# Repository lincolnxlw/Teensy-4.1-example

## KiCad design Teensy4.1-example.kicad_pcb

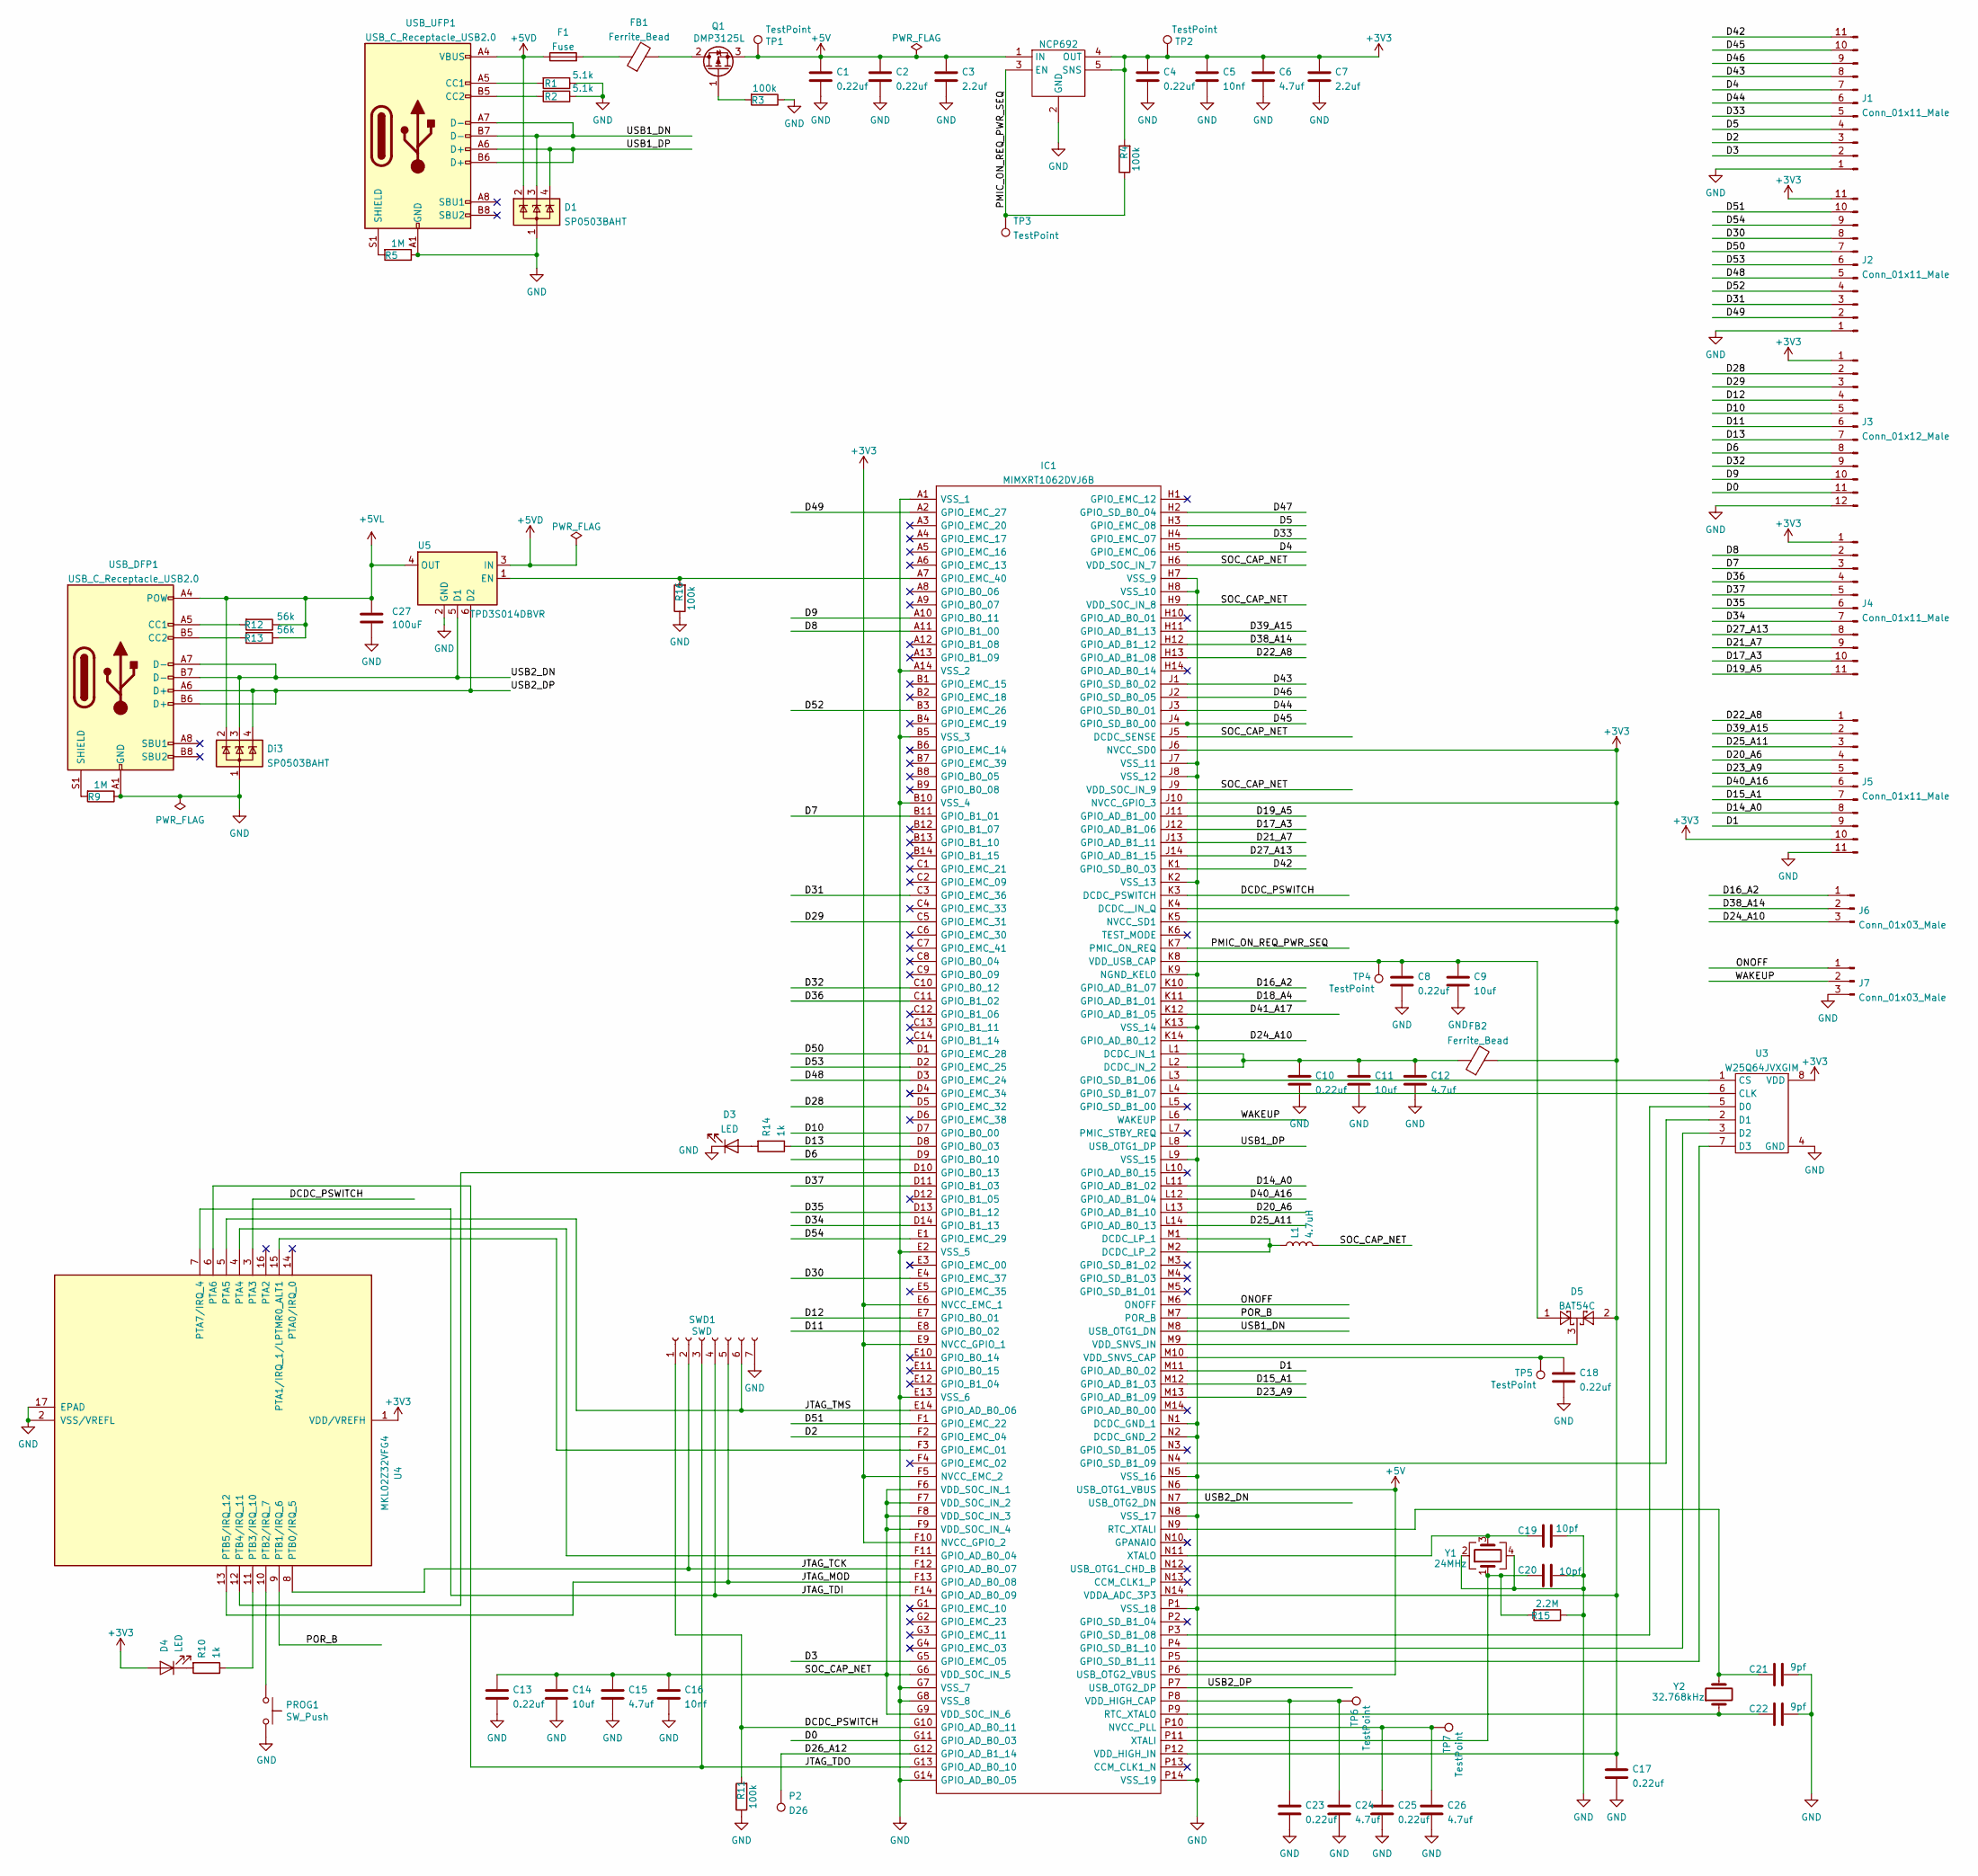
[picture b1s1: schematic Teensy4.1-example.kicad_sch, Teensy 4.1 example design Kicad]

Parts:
C1, C2, C4, C8, C10, C13, C17, C18, C23, C25: 0.22uf; C_0603_1608Metric; MPN CC0603KRX7R6BB224; LCSC C106216
C3, C7: 2.2uf; C_0603_1608Metric; MPN CL10B225KP8NNNC; LCSC C100082
C5, C16: 10nf; C_0603_1608Metric; MPN 0603B103K160CT; LCSC C163173
C6, C12, C15, C24, C26: 4.7uf; C_0603_1608Metric; MPN CL10B475KQ8NQNC; LCSC C107368
C9, C11, C14: 10uf; C_0805_2012Metric; MPN GRM21BR71A106KA73K; LCSC C2167686
C19, C20: 10pf; C_0603_1608Metric; MPN CC0603KRX7R6BB224; LCSC C1634
C21, C22: 9pf; C_0603_1608Metric; MPN GRM1885C1H9R0DA01D; LCSC C430713
C27: 100uF; C_1206_3216Metric; LCSC C883598
D1: SP0503BAHT; SOT-143; LCSC C3040626
D3, D4: LED; LED_0402_1005Metric; LCSC C264407
D5: BAT54C; SOT-23; LCSC C266596
Di3: SP0503BAHT; SOT-143; LCSC C3040626
F1: Fuse; R_0805_2012Metric; MPN 0ZCK0050FF2E; LCSC C5220829
FB1, FB2: Ferrite_Bead; R_0805_2012Metric; MPN FBMH2012HM121-T‎; LCSC C454098
IC1: MIMXRT1062DVJ6B; BGA196C80P14X14_1200X1200X152; Mouser Part Number 771-MIMXRT1062DVJ6B
J1, J2, J4, J5: Conn_01x11_Male; PinHeader_1x11_P2.54mm_Vertical
J3: Conn_01x12_Male; PinHeader_1x12_P2.54mm_Vertical
J6, J7: Conn_01x03_Male; PinHeader_1x03_P2.54mm_Vertical
L1: 4.7uH; C_0805_2012Metric; MPN LQM21PN4R7MGRD; LCSC C86090
NCP692: OnSemi NCP692, fixed version; DFN-6-1EP_3x3mm_P0.95mm_EP1.7x2.6mm; MPN NCP692MN33T2G; LCSC C145519
P2: D26; PinHeader_1x01_P1.00mm_Vertical
PROG1: SW_Push; KMR241GLFS; MPN KMR241GLFS; LCSC C221682
Q1: DMP3125L; SOT-23; LCSC C459542
R1, R2: 5.1k; R_0603_1608Metric; MPN RC0603FR-075K1L; LCSC C105580
R3, R4, R11, R16: 100k; R_0603_1608Metric; LCSC C15458
R5, R9: 1M; R_0603_1608Metric; LCSC C22935
R10, R14: 1k; R_0402_1005Metric; LCSC C11702
R12, R13: 56k; R_0603_1608Metric; MPN RMCF0603FT56K0; LCSC C23206
R15: 2.2M; R_0603_1608Metric; LCSC C18679
SWD1: SWD; PinHeader_1x07_P1.27mm_Vertical
TP1, TP2, TP3, TP4, TP5, TP6, TP7: TestPoint; TestPoint_Pad_D1.0mm
U3: W25Q64JVXGIM; XSON8_4x4mm; LCSC C5440778
U4: MKL02Z32VFG4; QFN-16-1EP_3x3mm_P0.5mm_EP1.8x1.8mm; MPN Custom firmware part
U5: TPD3S014DBVR; SOT-23-6; LCSC C87384
USB_DFP1: USB_C_Receptacle_USB2.0; TYPE-C-31-M-14; LCSC C223907
USB_UFP1: USB_C_Receptacle_USB2.0; TYPE-C-31-M-14; LCSC C223907
Y1: 24MHz; Crystal_SMD_Abracon_ABM3B-4Pin_5.0x3.2mm; LCSC C5544458
Y2: 32.768kHz; Crystal_SMD_2012-2Pin_2.0x1.2mm; MPN ABS06-32.768KHZ-9-1-T; LCSC C510776

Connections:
+3V3: C4.1, C5.1, C6.1, C7.1, C17.1, D4.2 (A), D5.2, FB2.2, IC1.E6 (NVCC_EMC_1), IC1.E9 (NVCC_GPIO_1), IC1.F5 (NVCC_EMC_2), IC1.F10 (NVCC_GPIO_2), IC1.J6 (NVCC_SD0), IC1.J10 (NVCC_GPIO_3), IC1.K4 (DCDC__IN_Q), IC1.K5 (NVCC_SD1), IC1.N14 (VDDA_ADC_3P3), IC1.P12 (VDD_HIGH_IN), J2.11, J3.1, J4.1, J5.10, NCP692.4 (OUT), NCP692.5 (SNS), R4.2, TP2.1, U3.8 (VDD), U4.1 (VDD/VREFH)
+5V: C1.1, C2.1, C3.1, IC1.N6 (USB_OTG1_VBUS), IC1.P6 (USB_OTG2_VBUS), NCP692.1 (IN), NCP692.6 (IN), Q1.3 (S), TP1.1
+5VD: D1.2 (K), F1.1, U5.3 (IN), USB_UFP1.A4 (VBUS), USB_UFP1.A9 (VBUS), USB_UFP1.B4 (VBUS), USB_UFP1.B9 (VBUS)
+5VL: C27.1, Di3.2 (K), R12.1, R13.1, U5.4 (OUT), USB_DFP1.A4 (POW), USB_DFP1.A9 (POW), USB_DFP1.B4 (POW), USB_DFP1.B9 (POW)
/D0: IC1.G11 (GPIO_AD_B0_03), J3.11
/D1: IC1.M11 (GPIO_AD_B0_02), J5.9
/D2: IC1.F2 (GPIO_EMC_04), J1.3
/D3: IC1.G5 (GPIO_EMC_05), J1.2
/D4: IC1.H5 (GPIO_EMC_06), J1.7
/D5: IC1.H3 (GPIO_EMC_08), J1.4
/D6: IC1.D9 (GPIO_B0_10), J3.8
/D7: IC1.B11 (GPIO_B1_01), J4.3
/D8: IC1.A11 (GPIO_B1_00), J4.2
/D9: IC1.A10 (GPIO_B0_11), J3.10
/D10: IC1.D7 (GPIO_B0_00), J3.5
/D11: IC1.E8 (GPIO_B0_02), J3.6
/D12: IC1.E7 (GPIO_B0_01), J3.4
/D13: IC1.D8 (GPIO_B0_03), J3.7, R14.1
/D14_A0: IC1.L11 (GPIO_AD_B1_02), J5.8
/D15_A1: IC1.M12 (GPIO_AD_B1_03), J5.7
/D16_A2: IC1.K10 (GPIO_AD_B1_07), J6.1
/D17_A3: IC1.J12 (GPIO_AD_B1_06), J4.10
/D18_A4: IC1.K11 (GPIO_AD_B1_01)
/D19_A5: IC1.J11 (GPIO_AD_B1_00), J4.11
/D20_A6: IC1.L13 (GPIO_AD_B1_10), J5.4
/D21_A7: IC1.J13 (GPIO_AD_B1_11), J4.9
/D22_A8: IC1.H13 (GPIO_AD_B1_08), J5.1
/D23_A9: IC1.M13 (GPIO_AD_B1_09), J5.5
/D24_A10: IC1.K14 (GPIO_AD_B0_12), J6.3
/D25_A11: IC1.L14 (GPIO_AD_B0_13), J5.3
/D26_A12: IC1.G12 (GPIO_AD_B1_14), P2.1
/D27_A13: IC1.J14 (GPIO_AD_B1_15), J4.8
/D28: IC1.D5 (GPIO_EMC_32), J3.2
/D29: IC1.C5 (GPIO_EMC_31), J3.3
/D30: IC1.E4 (GPIO_EMC_37), J2.8
/D31: IC1.C3 (GPIO_EMC_36), J2.3
/D32: IC1.C10 (GPIO_B0_12), J3.9
/D33: IC1.H4 (GPIO_EMC_07), J1.5
/D34: IC1.D14 (GPIO_B1_13), J4.7
/D35: IC1.D13 (GPIO_B1_12), J4.6
/D36: IC1.C11 (GPIO_B1_02), J4.4
/D37: IC1.D11 (GPIO_B1_03), J4.5
/D38_A14: IC1.H12 (GPIO_AD_B1_12), J6.2
/D39_A15: IC1.H11 (GPIO_AD_B1_13), J5.2
/D40_A16: IC1.L12 (GPIO_AD_B1_04), J5.6
/D41_A17: IC1.K12 (GPIO_AD_B1_05)
/D42: IC1.K1 (GPIO_SD_B0_03), J1.11
/D43: IC1.J1 (GPIO_SD_B0_02), J1.8
/D44: IC1.J3 (GPIO_SD_B0_01), J1.6
/D45: IC1.J4 (GPIO_SD_B0_00), J1.10
/D46: IC1.J2 (GPIO_SD_B0_05), J1.9
/D47: IC1.H2 (GPIO_SD_B0_04)
/D48: IC1.D3 (GPIO_EMC_24), J2.5
/D49: IC1.A2 (GPIO_EMC_27), J2.2
/D50: IC1.D1 (GPIO_EMC_28), J2.7
/D51: IC1.F1 (GPIO_EMC_22), J2.10
/D52: IC1.B3 (GPIO_EMC_26), J2.4
/D53: IC1.D2 (GPIO_EMC_25), J2.6
/D54: IC1.E1 (GPIO_EMC_29), J2.9
/DCDC_PSWITCH: IC1.G10 (GPIO_AD_B0_11), IC1.K3 (DCDC_PSWITCH), R11.2, SWD1.1, U4.3 (PTA3)
/JTAG_MOD: IC1.F13 (GPIO_AD_B0_08), SWD1.5, U4.13 (PTB5/IRQ_12)
/JTAG_TCK: IC1.F12 (GPIO_AD_B0_07), SWD1.2, U4.8 (PTB0/IRQ_5)
/JTAG_TDI: IC1.F14 (GPIO_AD_B0_09), SWD1.4, U4.7 (PTA7/IRQ_4)
/JTAG_TDO: IC1.G13 (GPIO_AD_B0_10), SWD1.3, U4.6 (PTA6)
/JTAG_TMS: IC1.E14 (GPIO_AD_B0_06), SWD1.6, U4.5 (PTA5)
/ONOFF: IC1.M6 (ONOFF), J7.1
/PMIC_ON_REQ_PWR_SEQ: IC1.K7 (PMIC_ON_REQ), NCP692.3 (EN), R4.1, TP3.1
/POR_B: IC1.M7 (POR_B), U4.9 (PTB1/IRQ_6)
/SOC_CAP_NET: C13.1, C14.1, C15.1, C16.1, IC1.F6 (VDD_SOC_IN_1), IC1.F7 (VDD_SOC_IN_2), IC1.F8 (VDD_SOC_IN_3), IC1.F9 (VDD_SOC_IN_4), IC1.G6 (VDD_SOC_IN_5), IC1.G9 (VDD_SOC_IN_6), IC1.H6 (VDD_SOC_IN_7), IC1.H9 (VDD_SOC_IN_8), IC1.J5 (DCDC_SENSE), IC1.J9 (VDD_SOC_IN_9), L1.2
/USB1_DN: D1.3 (K), IC1.M8 (USB_OTG1_DN), USB_UFP1.A7 (D-), USB_UFP1.B7 (D-)
/USB1_DP: D1.4 (K), IC1.L8 (USB_OTG1_DP), USB_UFP1.A6 (D+), USB_UFP1.B6 (D+)
/USB2_DN: Di3.3 (K), IC1.N7 (USB_OTG2_DN), U5.5 (D1), USB_DFP1.A7 (D-), USB_DFP1.B7 (D-)
/USB2_DP: Di3.4 (K), IC1.P7 (USB_OTG2_DP), U5.6 (D2), USB_DFP1.A6 (D+), USB_DFP1.B6 (D+)
/WAKEUP: IC1.L6 (WAKEUP), J7.2
GND: C1.2, C2.2, C3.2, C4.2, C5.2, C6.2, C7.2, C8.2, C9.2, C10.2, C11.2, C12.2, C13.2, C14.2, C15.2, C16.2, C17.2, C18.2, C19.2, C20.2, C21.2, C22.2, C23.2, C24.2, C25.2, C26.2, C27.2, D1.1 (A), D3.1 (K), Di3.1 (A), IC1.A1 (VSS_1), IC1.A14 (VSS_2), IC1.B5 (VSS_3), IC1.B10 (VSS_4), IC1.E2 (VSS_5), IC1.E13 (VSS_6), IC1.G7 (VSS_7), IC1.G8 (VSS_8), IC1.G14 (GPIO_AD_B0_05), IC1.H7 (VSS_9), IC1.H8 (VSS_10), IC1.J7 (VSS_11), IC1.J8 (VSS_12), IC1.K2 (VSS_13), IC1.K9 (NGND_KEL0), IC1.K13 (VSS_14), IC1.L9 (VSS_15), IC1.N1 (DCDC_GND_1), IC1.N2 (DCDC_GND_2), IC1.N5 (VSS_16), IC1.N8 (VSS_17), IC1.P1 (VSS_18), IC1.P14 (VSS_19), J1.1, J2.1, J3.12, J5.11, J7.3, NCP692.2 (GND), NCP692.7 (GND), PROG1.2, R1.1, R2.1, R3.1, R5.1, R9.1, R11.1, R15.1, R16.1, SWD1.7, U3.4 (GND), U4.2 (VSS/VREFL), U4.17 (EPAD), U5.2 (GND), USB_DFP1.A1 (GND), USB_DFP1.A12 (GND), USB_DFP1.B1 (GND), USB_DFP1.B12 (GND), USB_UFP1.A1 (GND), USB_UFP1.A12 (GND), USB_UFP1.B1 (GND), USB_UFP1.B12 (GND), Y1.2, Y1.4
unnamed: D3.2 (A), R14.2
unnamed: D4.1 (K), R10.2
unnamed: F1.2, FB1.1
unnamed: C10.1, C11.1, C12.1, FB2.1, IC1.L1 (DCDC_IN_1), IC1.L2 (DCDC_IN_2)
unnamed: IC1.M1 (DCDC_LP_1), IC1.M2 (DCDC_LP_2), L1.1
unnamed: IC1.F11 (GPIO_AD_B0_04), U4.4 (PTA4)
unnamed: IC1.D10 (GPIO_B0_13), U4.12 (PTB4/IRQ_11)
unnamed: IC1.F3 (GPIO_EMC_01), U4.15 (PTA1/IRQ_1/LPTMR0_ALT1)
unnamed: IC1.A7 (GPIO_EMC_40), R16.2, U5.1 (EN)
unnamed: IC1.L3 (GPIO_SD_B1_06), U3.1 (CS)
unnamed: IC1.L4 (GPIO_SD_B1_07), U3.6 (CLK)
unnamed: IC1.P3 (GPIO_SD_B1_08), U3.5 (D0)
unnamed: IC1.N4 (GPIO_SD_B1_09), U3.2 (D1)
unnamed: IC1.P4 (GPIO_SD_B1_10), U3.3 (D2)
unnamed: IC1.P5 (GPIO_SD_B1_11), U3.7 (D3)
unnamed: C25.1, C26.1, IC1.P10 (NVCC_PLL), TP7.1
unnamed: C21.1, IC1.N9 (RTC_XTALI), Y2.2
unnamed: C22.1, IC1.P9 (RTC_XTALO), Y2.1
unnamed: C23.1, C24.1, IC1.P8 (VDD_HIGH_CAP), TP6.1
unnamed: C18.1, IC1.M10 (VDD_SNVS_CAP), TP5.1
unnamed: D5.3, IC1.M9 (VDD_SNVS_IN)
unnamed: C8.1, C9.1, D5.1, IC1.K8 (VDD_USB_CAP), TP4.1
unnamed: C20.1, IC1.P11 (XTALI), R15.2, Y1.1
unnamed: C19.1, IC1.N11 (XTALO), Y1.3
unnamed: FB1.2, Q1.2 (D)
unnamed: Q1.1 (G), R3.2
unnamed: PROG1.1, U4.10 (PTB2/IRQ_7)
unnamed: R10.1, U4.11 (PTB3/IRQ_10)
unnamed: R12.2, USB_DFP1.A5 (CC1)
unnamed: R13.2, USB_DFP1.B5 (CC2)
unnamed: R9.2, USB_DFP1.S1 (SHIELD)
unnamed: R1.2, USB_UFP1.A5 (CC1)
unnamed: R2.2, USB_UFP1.B5 (CC2)
unnamed: R5.2, USB_UFP1.S1 (SHIELD)

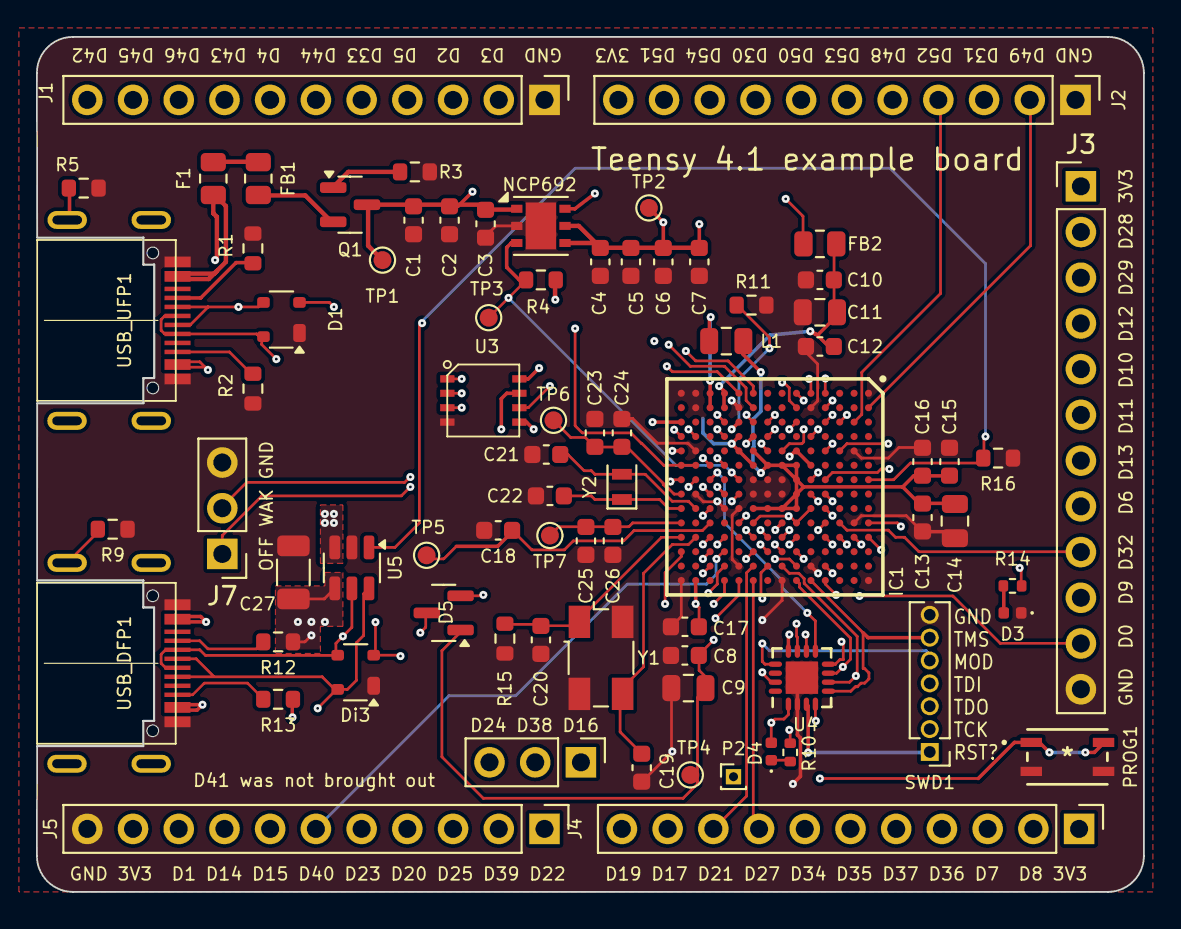
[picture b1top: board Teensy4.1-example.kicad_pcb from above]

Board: 4 copper layers, 61.5 x 47.5 mm, 76 parts (0 on the bottom side), 106 nets.

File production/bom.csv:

Designator,Footprint,Quantity,Value,LCSC Part #
"C1, C10, C13, C17, C18, C2, C23, C25, C4, C8",0603,10,0.22uf,C106216
"C11, C14, C9",0805,3,10uf,C2167686
"C12, C15, C24, C26, C6",0603,5,4.7uf,C107368
"C16, C5",0603,2,10nf,C163173
"C19, C20",0603,2,10pf,C1634
"C21, C22",0603,2,9pf,C430713
C27,1206,1,100uF,C883598
"C3, C7",0603,2,2.2uf,C100082
"D1, DI3",SOT-143,2,SP0503BAHT,C3040626
"D3, D4",0402,2,LED,C264407
D5,SOT-23,1,BAT54C,C266596
F1,0805,1,Fuse,C5220829
"FB1, FB2",0805,2,Ferrite_Bead,C454098
IC1,BGA196C80P14X14_1200X1200X152,1,MIMXRT1062DVJ6B,C3216699
"J1, J2, J4, J5",PinHeader_1x11_P2.54mm_Vertical,4,Conn_01x11_Male,
J3,PinHeader_1x12_P2.54mm_Vertical,1,Conn_01x12_Male,
"J6, J7",PinHeader_1x03_P2.54mm_Vertical,2,Conn_01x03_Male,
L1,0805,1,4.7uH,C86090
NCP692,DFN-6-1EP_3x3mm_P0.95mm_EP1.7x2.6mm,1,"OnSemi NCP692, fixed version",C145519
P2,PinHeader_1x01_P1.00mm_Vertical,1,D26,
PROG1,KMR241GLFS,1,SW_Push,C221682
Q1,SOT-23,1,DMP3125L,C459542
"R1, R2",0603,2,5.1k,C105580
"R10, R14",0402,2,1k,C11702
"R11, R16, R3, R4",0603,4,100k,C15458
"R12, R13",0603,2,56k,C23206
R15,0603,1,2.2M,C18679
"R5, R9",0603,2,1M,C22935
SWD1,PinHeader_1x07_P1.27mm_Vertical,1,SWD,
"TP1, TP2, TP3, TP4, TP5, TP6, TP7",TestPoint_Pad_D1.0mm,7,TestPoint,
U3,XSON8_4x4mm,1,W25Q64JVXGIM,C5440778
U4,QFN-16-1EP_3x3mm_P0.5mm_EP1.8x1.8mm,1,MKL02Z32VFG4,Custom firmware part
U5,SOT-23-6,1,TPD3S014DBVR,C87384
"USB_DFP1, USB_UFP1",TYPE-C-31-M-14,2,USB_C_Receptacle_USB2.0,C223907
Y1,Crystal_SMD_Abracon_ABM3B-4Pin_5.0x3.2mm,1,24MHz,C5544458
Y2,Crystal_SMD_2012-2Pin_2.0x1.2mm,1,32.768kHz,C510776

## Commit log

2024-11-21 Migrate to kicad8
2024-11-21 Schematics changes - Back to use TPD3S014DBVR for USB switch - Add JLC part numbers
2024-11-22 Update layout
2024-11-22 Remove the RGB LED
2024-11-22 Generate production files
2024-11-22 Update gitignore

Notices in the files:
parts and their libraries:
Copyright 2016 Accelerated Designs. All rights reserved.
